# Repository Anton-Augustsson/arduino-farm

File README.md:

# arduino-farm
## Arduino 
the code is in arduino folder, library is not inluded.

## Kicad
is in kicad, BOM is not included, library is not inluded.

## Seed
is the PCB pruduser. Allfiles is abluge to be sent inorder to get valid cad drwing.

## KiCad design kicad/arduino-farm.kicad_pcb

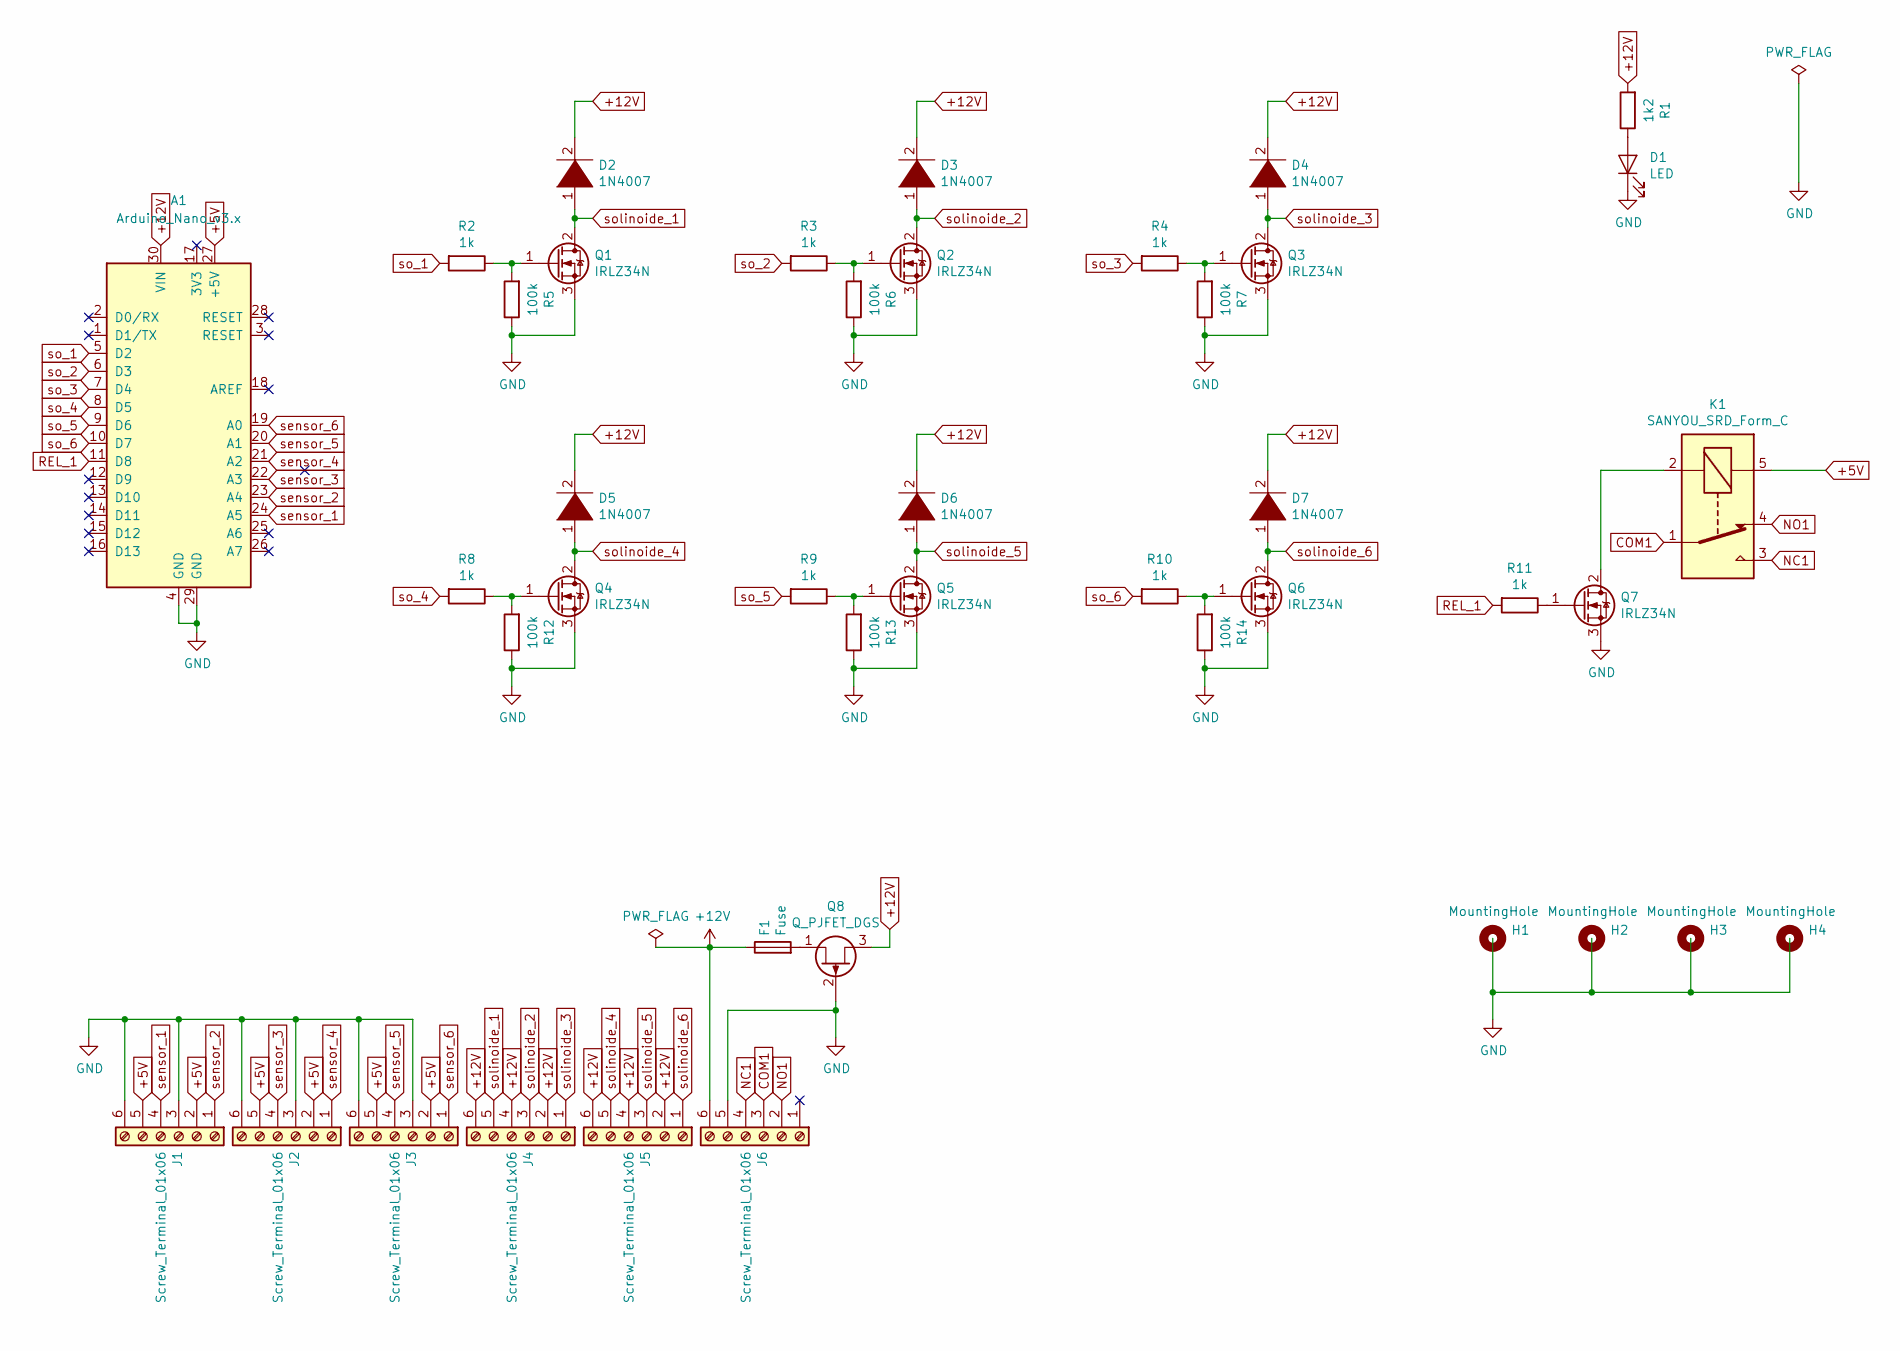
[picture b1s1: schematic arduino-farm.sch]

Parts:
A1: Arduino_Nano_v3.x; Arduino_Nano
D1: LED; LED_D3.0mm
D2, D3, D4, D5, D6, D7: 1N4007; D_DO-41_SOD81_P7.62mm_Horizontal
F1: Fuse; Fuseholder_Blade_ATO_Littelfuse_Pudenz_2_Pin
H1, H2, H3, H4: MountingHole; MountingHole_3.2mm_M3_DIN965
J1, J2, J3, J4, J5, J6: Screw_Terminal_01x06; TerminalBlock_Phoenix_MKDS-1,5-6-5.08_1x06_P5.08mm_Horizont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
K1: SANYOU_SRD_Form_C; Relay_SPDT_SANYOU_SRD_Series_Form_C
Q1, Q2, Q3, Q4, Q5, Q6, Q7: IRLZ34N; TO-220-3_Vertical
Q8: Q_PJFET_DGS; TO-220-3_Vertical
R1: 1k2; R_Axial_DIN0207_L6.3mm_D2.5mm_P10.16mm_Horizontal
R2, R3, R4, R8, R9, R10, R11: 1k; R_Axial_DIN0207_L6.3mm_D2.5mm_P10.16mm_Horizontal
R5, R6, R7, R12, R13, R14: 100k; R_Axial_DIN0207_L6.3mm_D2.5mm_P10.16mm_Horizontal

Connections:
+5V: A1.27 (+5V), J1.2, J1.5, J2.2, J2.5, J3.2, J3.5, K1.5
+12V: A1.30 (VIN), D2.2 (A), D3.2 (A), D4.2 (A), D5.2 (A), D6.2 (A), D7.2 (A), F1.1, J4.2, J4.4, J4.6, J5.2, J5.4, J5.6, J6.6, Q8.3 (S), R1.2
COM1: J6.3, K1.1
GND: A1.4 (GND), A1.29 (GND), D1.1 (K), J1.3, J1.6, J2.3, J2.6, J3.3, J3.6, J6.5, Q1.3 (S), Q2.3 (S), Q3.3 (S), Q4.3 (S), Q5.3 (S), Q6.3 (S), Q7.3 (S), Q8.2 (G), R5.1, R6.1, R7.1, R12.1, R13.1, R14.1
NC1: J6.4, K1.3
NO1: J6.2, K1.4
unnamed: D1.2 (A), R1.1
unnamed: F1.2, Q8.1 (D)
unnamed: K1.2, Q7.2 (D)
unnamed: Q1.1 (G), R2.1, R5.2
unnamed: Q2.1 (G), R3.1, R6.2
unnamed: Q3.1 (G), R4.1, R7.2
unnamed: Q4.1 (G), R8.1, R12.2
unnamed: Q5.1 (G), R9.1, R13.2
unnamed: Q6.1 (G), R10.1, R14.2
unnamed: Q7.1 (G), R11.1
REL_1: A1.11 (D8), R11.2
sensor_1: A1.24 (A5), J1.4
sensor_2: A1.23 (A4), J1.1
sensor_3: A1.22 (A3), J2.4
sensor_4: A1.21 (A2), J2.1
sensor_5: A1.20 (A1), J3.4
sensor_6: A1.19 (A0), J3.1
so_1: A1.5 (D2), R2.2
so_2: A1.6 (D3), R3.2
so_3: A1.7 (D4), R4.2
so_4: A1.8 (D5), R8.2
so_5: A1.9 (D6), R9.2
so_6: A1.10 (D7), R10.2
solinoide_1: D2.1 (K), J4.5, Q1.2 (D)
solinoide_2: D3.1 (K), J4.3, Q2.2 (D)
solinoide_3: D4.1 (K), J4.1, Q3.2 (D)
solinoide_4: D5.1 (K), J5.5, Q4.2 (D)
solinoide_5: D6.1 (K), J5.3, Q5.2 (D)
solinoide_6: D7.1 (K), J5.1, Q6.2 (D)

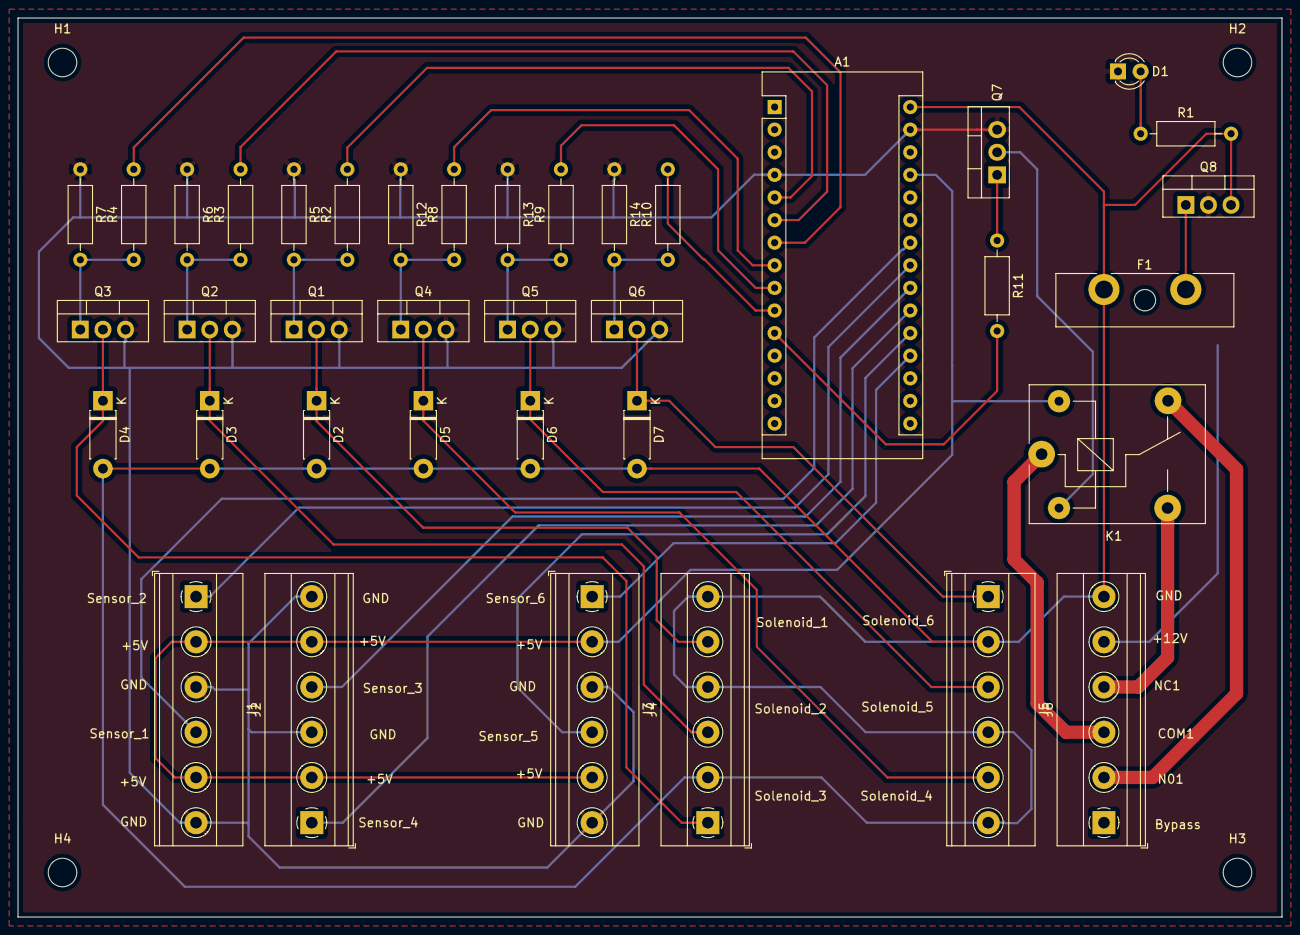
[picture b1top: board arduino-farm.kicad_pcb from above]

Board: 2 copper layers, 142.0 x 101.0 mm, 42 parts (0 on the bottom side), 35 nets.

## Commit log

2020-02-18 Readme update
